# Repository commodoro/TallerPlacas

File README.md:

# Taller de Soldadura IEEE UPCT

En este repositorio:

- Placa
- Lista de materiales
- Instrucciones en presentación

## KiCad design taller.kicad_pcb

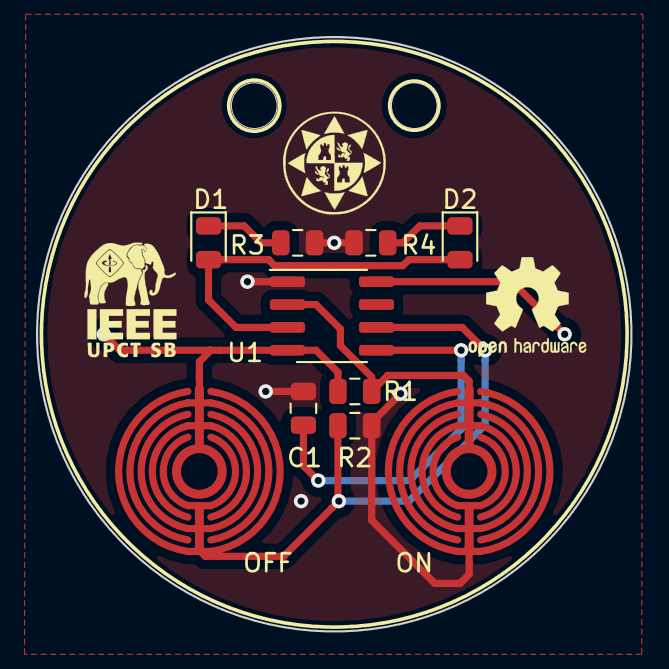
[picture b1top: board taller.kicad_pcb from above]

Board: 2 copper layers, 33.0 x 33.0 mm, 11 parts (1 on the bottom side), 8 nets.

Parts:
BATTERY: CR2032; BatteryHolder_Keystone_3002_1x2032
C1: C; C_0805_2012Metric
D1, D2: LED; D_0805_2012Metric
OFF: OFF; g2
ON: ON; g2
R1, R2: 3M3; R_0805_2012Metric
R3, R4: 130; R_0805_2012Metric
U1: TLC555; SOIC-8_3.9x4.9mm_P1.27mm

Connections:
GND: BATTERY.2, C1.2, ON.1, R2.2, R3.1, R4.2, U1.1
unnamed: BATTERY.1, OFF.2, R1.1, U1.4, U1.8
unnamed: C1.1, U1.5
unnamed: D1.1, R3.2
unnamed: D1.2, D2.2, U1.3
unnamed: D2.1, R4.1
unnamed: OFF.1, R2.1, U1.6
unnamed: ON.2, R1.2, U1.2

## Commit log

2021-10-06 Diseño con el logo de cartagena
